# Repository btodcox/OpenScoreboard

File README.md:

#OpenScoreboard
## An Open Source Wireless Swimming Scoreboard that can be easily modified for other sports

OpenScoreboard is an Eagle Scout Project completed by David Cox in 2014.  The beneficiary/sponsoring organization was the Gleannloch Gators Swim Team.

The scoreboard hardware is designed around an Arduino derivative known as the Moteino from Felix Rusu at lowpowerlabs.com.  A program on a host PC implements a filewatcher.  When a new set of times is written to the hard drive of the host PC at the end of a completed heat, the program parses the times, calculates the swimmers tentative official time, determines the order of finish, and passes the data to a USB attached Moteino.  This Moteino then passes the information wirelessly to the scoreboard where it is displayed.  The results of a given heat are displayed until the next heat completes.  While this is a bit different than typical swimming scoreboards (which reset as soon as the next heat starts), it allows the coaches and swimmers to focus on the logistics of finishing one heat and beginning the next heat without having to hurriedly view the scoreboard.

License Info:

<br /><span xmlns:dct="http://purl.org/dc/terms/" property="dct:title">OpenScoreboard</span> by <a xmlns:cc="http://creativecommons.org/ns#" href="https://github.com/btodcox/Scoreboard" property="cc:attributionName" rel="cc:attributionURL">B Tod Cox & David Cox</a> is licensed under a <a rel="license" href="http://creativecommons.org/licenses/by-sa/4.0/">Creative Commons Attribution-ShareAlike 4.0 International License</a>. A copy of the license is available at the provided link. 

Portions of this project leverages other projects; attributions are included in the repository.

## Bill of Materials for 8-Lane Wireless Scoreboard

The estimated total cost for an 8-lane OpenScoreboard is ~$2500.

Custom PCA (a total of N+1 Custom PCAs are needed for an N-lane scoreboard)

*   9x Custom Scoreboard PCB (Eagle CAD files included in repository)
*   18X 74AHCT245D Octal Transceiver SOIC-20 ([Mouser 771-AHCT245D118](http://www.mouser.com/Search/ProductDetail.aspx?R=74AHCT245D,118virtualkey66800000virtualkey771-AHCT245D118))
*   2.1mm x 5.5mm DC barrel jack ([Mouser 163-7620E-E](http://www.mouser.com/Search/ProductDetail.aspx?R=163-7620E-Evirtualkey11180000virtualkey163-7620E-E))
*   18X dual row 2x5 0.1" female header ([Mouser 571-215309-5](http://www.mouser.com/Search/ProductDetail.aspx?R=215309-5virtualkey57100000virtualkey571-215309-5))
*   ~250X Breakaway 0.1" Male Headers ([Mouser 649-54101-S08-00](http://www.mouser.com/Search/ProductDetail.aspx?R=54101-S08-00virtualkey64910000virtualkey649-54101-S08-00))
*   18X 0.1uF 16V 10% X7R 0603 capacitor ([Mouser 80-C0603C104K4R7411](http://www.mouser.com/Search/ProductDetail.aspx?R=C0603C104K4RAC7411virtualkey64600000virtualkey80-C0603C104K4R7411))

Electronic Parts

*   9X [Moteino Arduino clone with tranceiver and flash](http://lowpowerlab.com/moteino/#pinout)
*   1X [USB Moteino with transciever and no flash](http://lowpowerlab.com/moteino/#pinout)
*   68X 16x24 Red LED Matrix Panel Chainable HT1632C Driver ([Adafruit part #555](http://www.adafruit.com/products/555))
*   408X 1206 4RNet 27 Ohm 5% (to increase brightness of LED panels) ([Mouser 667-EXB-38V270JV](http://www.mouser.com/Search/ProductDetail.aspx?R=EXB-38V270JVvirtualkey66720000virtualkey667-EXB-38V270JV))
*   84X 2x5 IDC ribbon cable male connectors (need a different part number as I don't like the ones that I last ordered from Mouser)
*   ~50ft Flat Cables 28 AWG Ribbon .050 Zip 10 Cond ([Mouser 523-191-2801-110FT](http://www.mouser.com/Search/ProductDetail.aspx?R=191-2801-110FTvirtualkey52320000virtualkey523-191-2801-110FT))
*   4X 5V 10A switching power supply ([Adafruit part #658](http://www.adafruit.com/product/658))
*   3X 2-Way 2.1mm DC Barrel Jack Splitter Squid ([Adafruit part #1351](http://www.adafruit.com/product/1351))
*   Heavy gauge wire for connecting three lanes together (could not find a squid splitter long enough for Event/Heat + 2 lanes)
*   Surge protector
*   Mini-USB to USB cable
*   Small plastic box for USB Moteino

Case/Mechanical Structure

*   18X 3/4 in. x 1/2 in. x 36 in. Aluminum Flat Angle with 1/16 in. Thick ([Home Depot](http://www.homedepot.com/p/Crown-Bolt-3-4-in-x-1-2-in-x-36-in-Aluminum-Flat-Angle-with-1-16-in-Thick-43650/202183475)/Lowes/etc)
*   2X Steelworks 6-ft L x -3/4-in W x -3/4-in H Aluminum Plain Square Tube ([Lowes](http://www.lowes.com/pd_215691-37672-11388_0__)/Home Depot/etc)
*   Red Cast Acrylic (Aero-Shield Plastics in Houston)
*   1x6 Poplar S4S boards for case (Home Depot/Lowes/etc)
*   272X 4-40 x 1" female/female hex binding post ([Mouser 534-2205](http://www.mouser.com/Search/ProductDetail.aspx?R=2205virtualkey53400000virtualkey534-2205))
*   544x 4-40 3/8" phillips head screws ([Mouser 534-9901](http://www.mouser.com/Search/ProductDetail.aspx?R=9901virtualkey53400000virtualkey534-9901))
*   1-1/4 in. Coarse Zinc-Plated Steel Square-Head Pocket Screws (100-Pack) ([Home Depot](http://www.homedepot.com/p/Kreg-1-1-4-in-Coarse-Zinc-Plated-Steel-Square-Head-Pocket-Screws-100-Pack-SML-C125-100/100572559))
*   1X 1/4 in. 5 ft. x 5ft Baltic Birch Plywood-Grade A ([Houston Hardwoods](http://www.houstonhardwoods.net/))
*   Paint for wood (less than 1/2 pint is needed to cover wood)
*   Exterior grade urethane for back of plywood
*   Black matte spray paint for interior of plywood and aluminum

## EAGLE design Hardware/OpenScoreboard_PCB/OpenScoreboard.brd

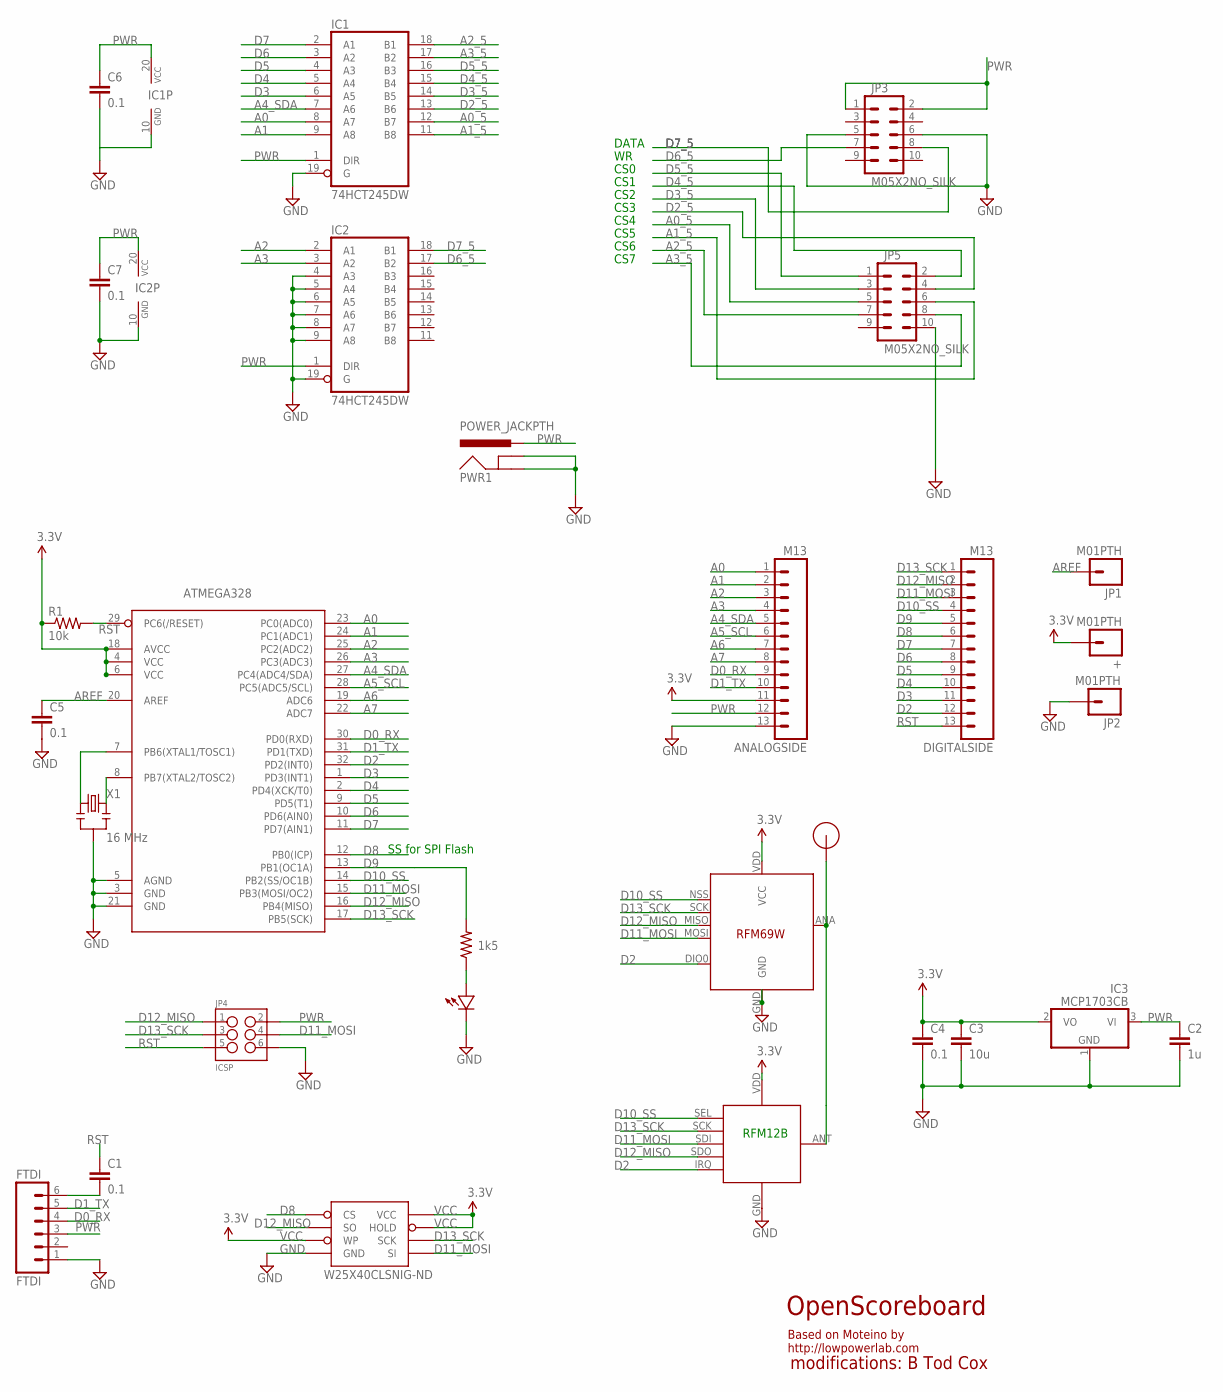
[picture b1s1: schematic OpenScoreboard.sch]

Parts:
+: M01PTH; 1X01
ANALOGSIDE: M13; 1X13
ATMEGA328: ATMega-328; TQFP32-08
C1, C4, C5, C6, C7: 0.1; 0603-CAP
C2: 1u; 0603-CAP
C3: 10u; 0805-CAP
DIGITALSIDE: M13; 1X13
FTDI: FTDI; 1X06
IC1, IC2: 74HCT245DW; SO20W
IC3: MCP1703CB; SOT23
JP1, JP2: M01PTH; 1X01
JP3, JP5: M05X2NO_SILK; 2X5_NOSILK
JP4: ICSP; 2X3_POGO
PWR1: POWER_JACKPTH; POWER_JACK_PTH
R1: 10k; 0603-RES
R2: 1k5; 0603-RES
RFM12B: RFM12B_MINPADS; RFM12B-MINPADS
U$1: RFM12B_ANTENNA; RFM12B-ANTENNA
U$2: LED0603; 0603-LED
U$5: RFM69; RFM69W-MINPADS
W25X40CLSNIG-ND: AT25F512BWIDE_5.3MM; SO08WIDE
X1: 16 MHz; RESONATOR-SMD

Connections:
A0: ANALOGSIDE.1, ATMEGA328.23 (PC0(ADC0)), IC1.8 (A7)
A0_5: IC1.12 (B7), JP5.5
A1: ANALOGSIDE.2, ATMEGA328.24 (PC1(ADC1)), IC1.9 (A8)
A1_5: IC1.11 (B8), JP5.6
A2: ANALOGSIDE.3, ATMEGA328.25 (PC2(ADC2)), IC2.2 (A1)
A2_5: IC1.18 (B1), JP5.7
A3: ANALOGSIDE.4, ATMEGA328.26 (PC3(ADC3)), IC2.3 (A2)
A3_5: IC1.17 (B2), JP5.8
A4_SDA: ANALOGSIDE.5, ATMEGA328.27 (PC4(ADC4/SDA)), IC1.7 (A6)
A5_SCL: ANALOGSIDE.6, ATMEGA328.28 (PC5(ADC5/SCL))
A6: ANALOGSIDE.7, ATMEGA328.19 (ADC6)
A7: ANALOGSIDE.8, ATMEGA328.22 (ADC7)
AREF: ATMEGA328.20 (AREF), C5.1, JP1.1
D0_RX: ANALOGSIDE.9, ATMEGA328.30 (PD0(RXD)), FTDI.4
D1_TX: ANALOGSIDE.10, ATMEGA328.31 (PD1(TXD)), FTDI.5
D2: ATMEGA328.32 (PD2(INT0)), DIGITALSIDE.12, RFM12B.IRQ, U$5.DIO0
D2_5: IC1.13 (B6), JP5.4
D3: ATMEGA328.1 (PD3(INT1)), DIGITALSIDE.11, IC1.6 (A5)
D3_5: IC1.14 (B5), JP5.3
D4: ATMEGA328.2 (PD4(XCK/T0)), DIGITALSIDE.10, IC1.5 (A4)
D4_5: IC1.15 (B4), JP5.2
D5: ATMEGA328.9 (PD5(T1)), DIGITALSIDE.9, IC1.4 (A3)
D5_5: IC1.16 (B3), JP5.1
D6: ATMEGA328.10 (PD6(AIN0)), DIGITALSIDE.8, IC1.3 (A2)
D6_5: IC2.17 (B2), JP3.7
D7: ATMEGA328.11 (PD7(AIN1)), DIGITALSIDE.7, IC1.2 (A1)
D7_5: IC2.18 (B1), JP3.8
D8: ATMEGA328.12 (PB0(ICP)), DIGITALSIDE.6, W25X40CLSNIG-ND.1 (CS)
D9: ATMEGA328.13 (PB1(OC1A)), DIGITALSIDE.5, R2.2
D10_SS: ATMEGA328.14 (PB2(SS/OC1B)), DIGITALSIDE.4, RFM12B.SEL, U$5.NSS (SEL)
D11_MOSI: ATMEGA328.15 (PB3(MOSI/OC2)), DIGITALSIDE.3, JP4.P$4 (4), RFM12B.SDI (SDI/MOSI), U$5.MOSI, W25X40CLSNIG-ND.5 (SI)
D12_MISO: ATMEGA328.16 (PB4(MISO)), DIGITALSIDE.2, JP4.P$1 (1), RFM12B.SDO (SDO/MISO), U$5.MISO, W25X40CLSNIG-ND.2 (SO)
D13_SCK: ATMEGA328.17 (PB5(SCK)), DIGITALSIDE.1, JP4.P$3 (3), RFM12B.SCK, U$5.SCK, W25X40CLSNIG-ND.6 (SCK)
GND: ANALOGSIDE.13, ATMEGA328.3 (GND), ATMEGA328.5 (AGND), ATMEGA328.21 (GND), C2.2, C3.2, C4.2, C5.2, C6.2, C7.2, FTDI.1, IC1.10 (GND), IC1.19 (G), IC2.4 (A3), IC2.5 (A4), IC2.6 (A5), IC2.7 (A6), IC2.8 (A7), IC2.9 (A8), IC2.10 (GND), IC2.19 (G), IC3.1 (GND), JP2.1, JP3.5, JP3.6, JP4.P$6 (6), JP5.10, PWR1.GND, PWR1.GNDBREAK, RFM12B.GND, U$2.MINUS, U$5.GND, W25X40CLSNIG-ND.4 (GND), X1.2
unnamed: ATMEGA328.7 (PB6(XTAL1/TOSC1)), X1.1
unnamed: R2.1, U$2.PLUS
unnamed: RFM12B.ANT, U$1.P$1, U$5.ANA (ANT)
unnamed: C1.2, FTDI.6
unnamed: ATMEGA328.8 (PB7(XTAL2/TOSC2)), X1.3
PWR: ANALOGSIDE.12, C2.1, C6.1, C7.1, FTDI.3, IC1.1 (DIR), IC1.20 (VCC), IC2.1 (DIR), IC2.20 (VCC), IC3.3 (VI), JP3.1, JP3.2, JP4.P$2 (2), PWR1.PWR
RST: ATMEGA328.29 (PC6(/RESET)), C1.1, DIGITALSIDE.13, JP4.P$5 (5), R1.2
VCC: +.1, ANALOGSIDE.11, ATMEGA328.4 (VCC), ATMEGA328.6 (VCC), ATMEGA328.18 (AVCC), C3.1, C4.1, IC3.2 (VO), R1.1, RFM12B.VDD, U$5.VDD (VCC), W25X40CLSNIG-ND.3 (WP), W25X40CLSNIG-ND.7 (HOLD), W25X40CLSNIG-ND.8 (VCC)

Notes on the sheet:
OpenScoreboard
modifications: B Tod Cox
Based on Moteino by http://lowpowerlab.com
RFM12B
SS for SPI Flash
DATA
CS0
CS1
CS2
CS3
CS4
CS5
CS6
CS7

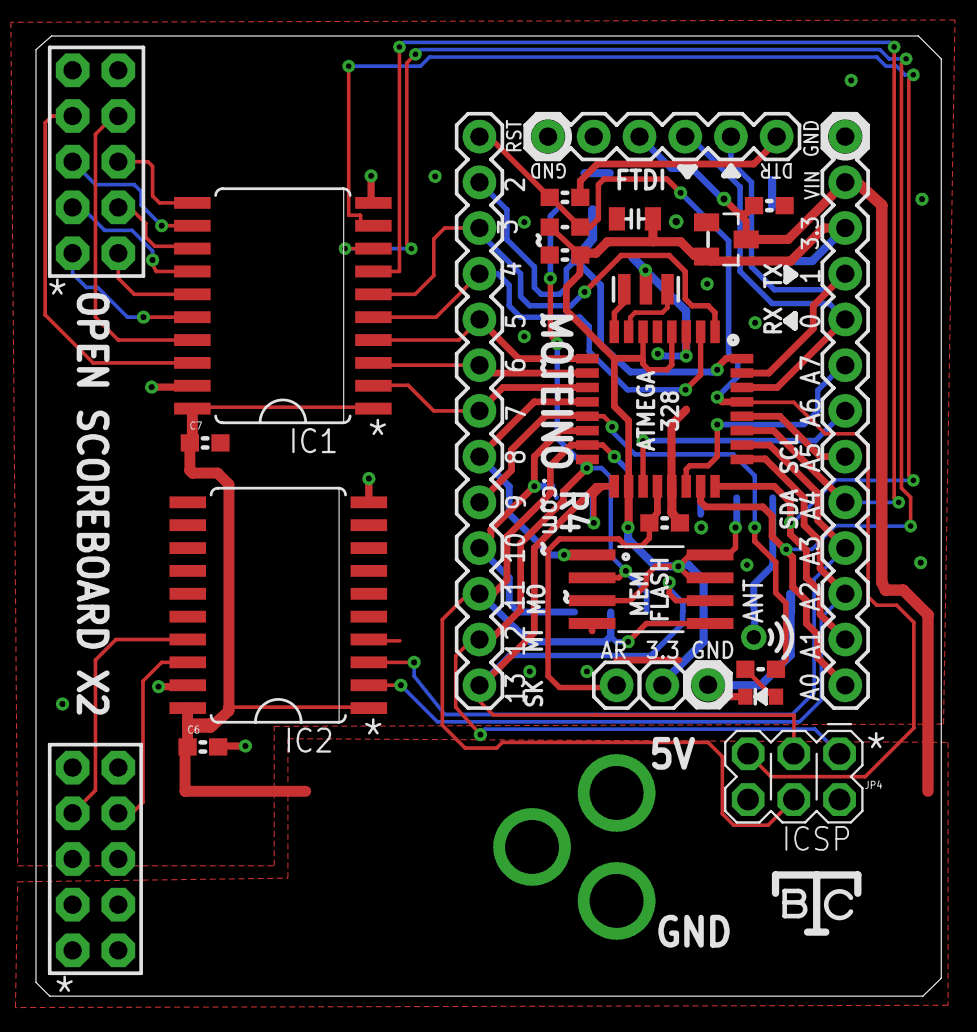
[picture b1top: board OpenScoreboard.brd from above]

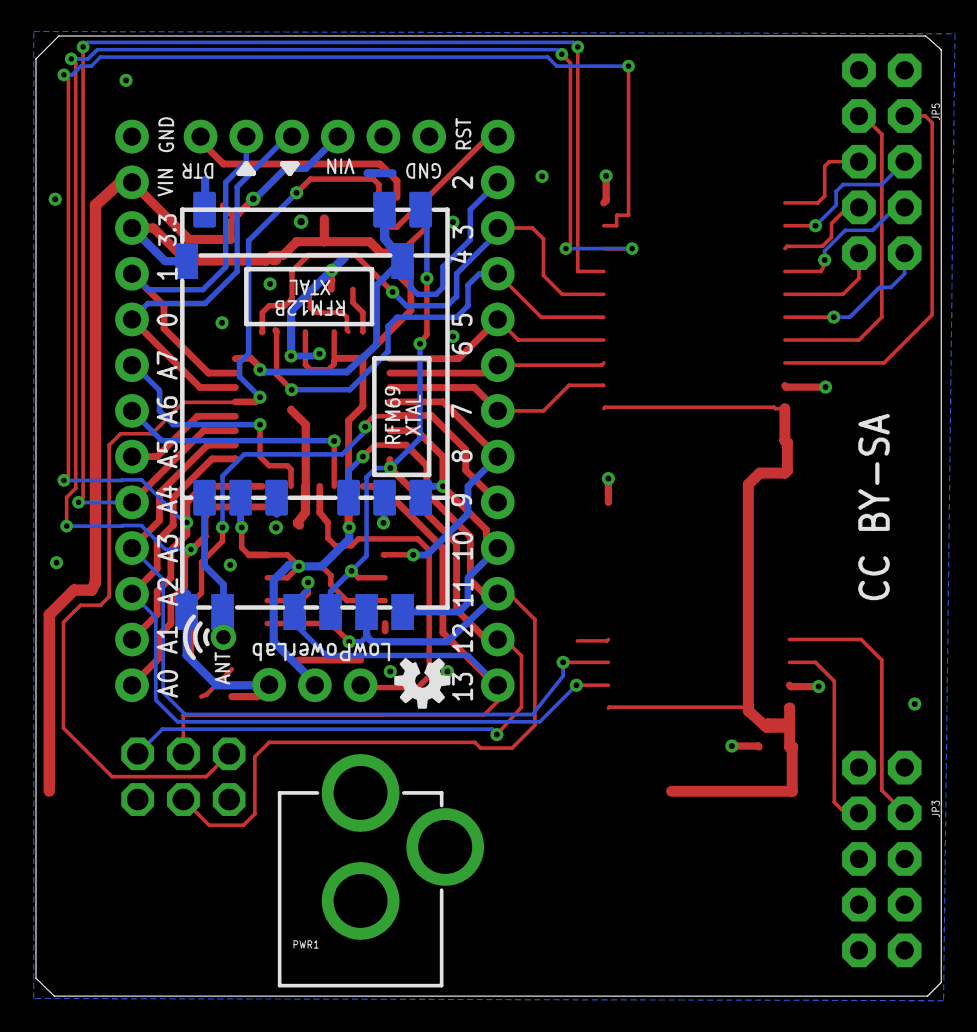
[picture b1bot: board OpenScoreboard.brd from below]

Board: 2 copper layers, 50.3 x 53.3 mm, 30 parts (6 on the bottom side), 42 nets.

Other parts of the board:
U$3: OSHW-LOGO-S

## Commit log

2016-06-03 Initial release
2016-06-03 removed unneeded files

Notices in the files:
Hardware/OpenScoreboard_PCB/OpenScoreboard.brd:
CC BY-SA
parts and their libraries:
SparkFun-Connectors: Licensing: CC v3.0 Share-Alike You are welcome to use this library for commercial purposes.
